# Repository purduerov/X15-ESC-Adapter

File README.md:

# Readme for X15-ESC-Adapter

Whenever you make a new part, download the datasheet and save it here _**and**_ with the part in the parts library

Always pull other people's changes before beginning to work
`git pull`

Be sure to push your changes after  working on them. Run:
1. `git add .` to add any files in this directory or a subdirectory
or `git add -u` to add any modified files
2. (Optional) `git clean -nX` to see what ignored files can be removed
	`git clean -fX` removes ignored files (Eagle backups)
3. `git commit -m "helpful commit message"` with a description of the work that you did
4. `git push` to push your work to github

Other helpful commands
* `git status` says information about modified and staged files
* `git log` shows the recent commits of the repository
* `git log filename.extension` show the recent commits for just that file
* `git checkout first-couple-letter-of-commit-id` lets you go back to a previous version
* `git checkout master` brings you back to the latest commit
* `git tag` lists the tags
* `git tag -a orderX -m "the version of the board placed for the X'th order"` tag a specific commit
* `git push --tags` needed to push tags to remote
* `git show orderX` show the commit log for the given tag
* `git checkout orderX` go back and interact with the files at the tagged commit

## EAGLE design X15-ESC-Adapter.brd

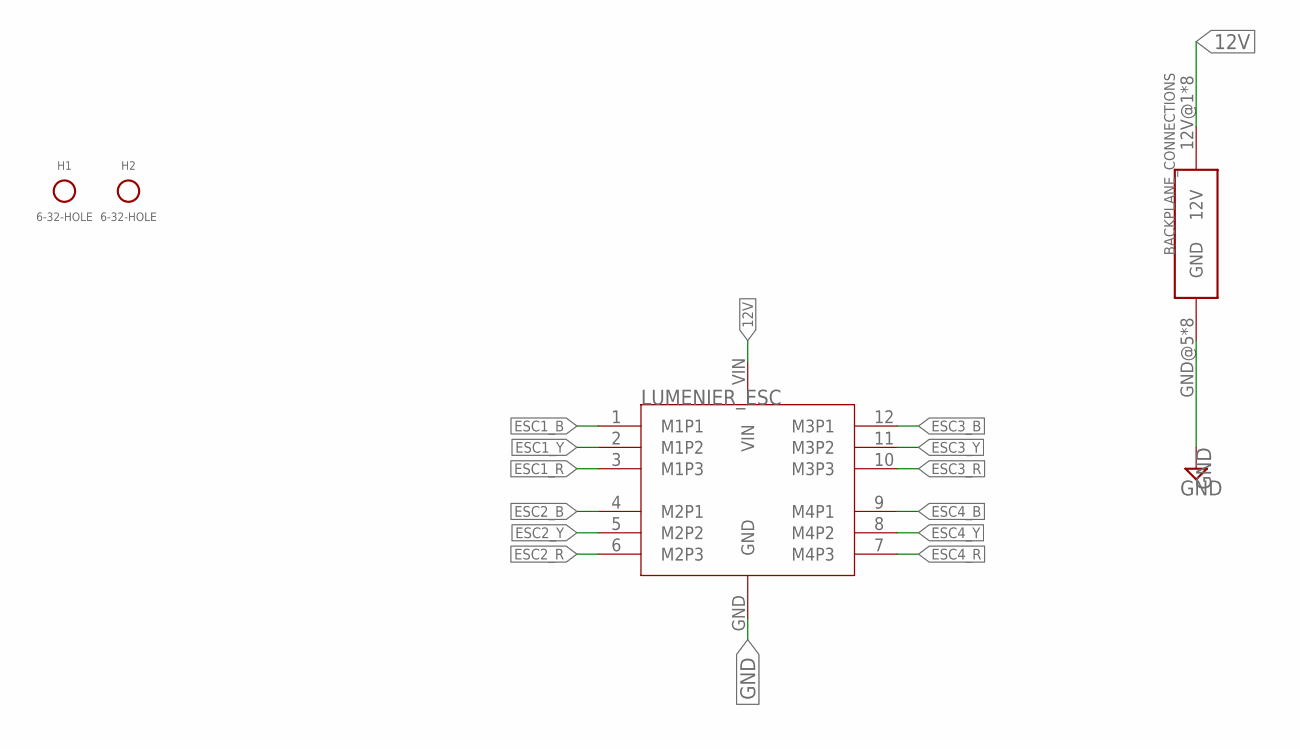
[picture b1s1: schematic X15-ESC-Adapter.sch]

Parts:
BACKPLANE_CONNECTIONS: IPS1-112-01-L-D; IPS1-BACKPLANE_ESC_ADAPTER_ESC_PWR
H1, H2: 6-32-HOLE
LUMENIER_ESC: LUMENIER

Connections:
12V: BACKPLANE_CONNECTIONS.12V@1 (12V), BACKPLANE_CONNECTIONS.12V@2 (12V), BACKPLANE_CONNECTIONS.12V@3 (12V), BACKPLANE_CONNECTIONS.12V@4 (12V), BACKPLANE_CONNECTIONS.12V@5 (12V), BACKPLANE_CONNECTIONS.12V@6 (12V), BACKPLANE_CONNECTIONS.12V@7 (12V), BACKPLANE_CONNECTIONS.12V@8 (12V), LUMENIER_ESC.VIN
ESC1_B: LUMENIER_ESC.1 (M1P1)
ESC1_R: LUMENIER_ESC.3 (M1P3)
ESC1_Y: LUMENIER_ESC.2 (M1P2)
ESC2_B: LUMENIER_ESC.4 (M2P1)
ESC2_R: LUMENIER_ESC.6 (M2P3)
ESC2_Y: LUMENIER_ESC.5 (M2P2)
ESC3_B: LUMENIER_ESC.12 (M3P1)
ESC3_R: LUMENIER_ESC.10 (M3P3)
ESC3_Y: LUMENIER_ESC.11 (M3P2)
ESC4_B: LUMENIER_ESC.9 (M4P1)
ESC4_R: LUMENIER_ESC.7 (M4P3)
ESC4_Y: LUMENIER_ESC.8 (M4P2)
GND: BACKPLANE_CONNECTIONS.GND@5 (GND), BACKPLANE_CONNECTIONS.GND@6 (GND), BACKPLANE_CONNECTIONS.GND@7 (GND), BACKPLANE_CONNECTIONS.GND@8 (GND), BACKPLANE_CONNECTIONS.GND@9 (GND), BACKPLANE_CONNECTIONS.GND@10 (GND), BACKPLANE_CONNECTIONS.GND@11 (GND), BACKPLANE_CONNECTIONS.GND@12 (GND), LUMENIER_ESC.GND

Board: 2 copper layers, 4 parts (0 on the bottom side), 2 nets, no tracks yet.

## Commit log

2022-10-01 1st Ver
2022-10-05 Initial Commit - New parts
2022-10-05 Second Version - Schematic V1
    Need schematic review
2022-10-12 Cleaned Up Final Version
2022-10-12 Cleaned up Final Version 2
2022-10-12 Board setup
2022-10-19 First Final Version of Board
    Finished first version of board
2022-10-22 Second FInal Version of Board
    Added vias
2022-10-22 Third Final Version
    Added names
2022-10-22 4th Final Version
    Fixed errors
2022-10-22 5th Final Version
    Fixed vias
2022-10-29 Parts Replaced with New Versions
2022-11-05 Fixed strange things
2022-11-17 Added feedback
2022-11-17 Adjusted thermals
2023-01-07 Fix wire stubs to polygons
2023-01-12 Adjusted the IPBT Footprint
2023-05-13 Complete ESC Adapter Design
2023-05-29 Update to v2

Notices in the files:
parts and their libraries:
SparkFun-Aesthetics: Licensing: Creative Commons ShareAlike 4.0 International - https://creativecommons.org/licenses/by-sa/4.0
